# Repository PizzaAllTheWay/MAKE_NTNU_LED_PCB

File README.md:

# MAKE_NTNU_LED_PCB
A light show PCB of LEDs in Real Time, PCB and Firmware made self with the use of external firmware libraries.

https://github.com/PizzaAllTheWay/MAKE_NTNU_LED_PCB/assets/42731091/1496fe23-2bfd-4109-9f32-cd6afeccfe6b

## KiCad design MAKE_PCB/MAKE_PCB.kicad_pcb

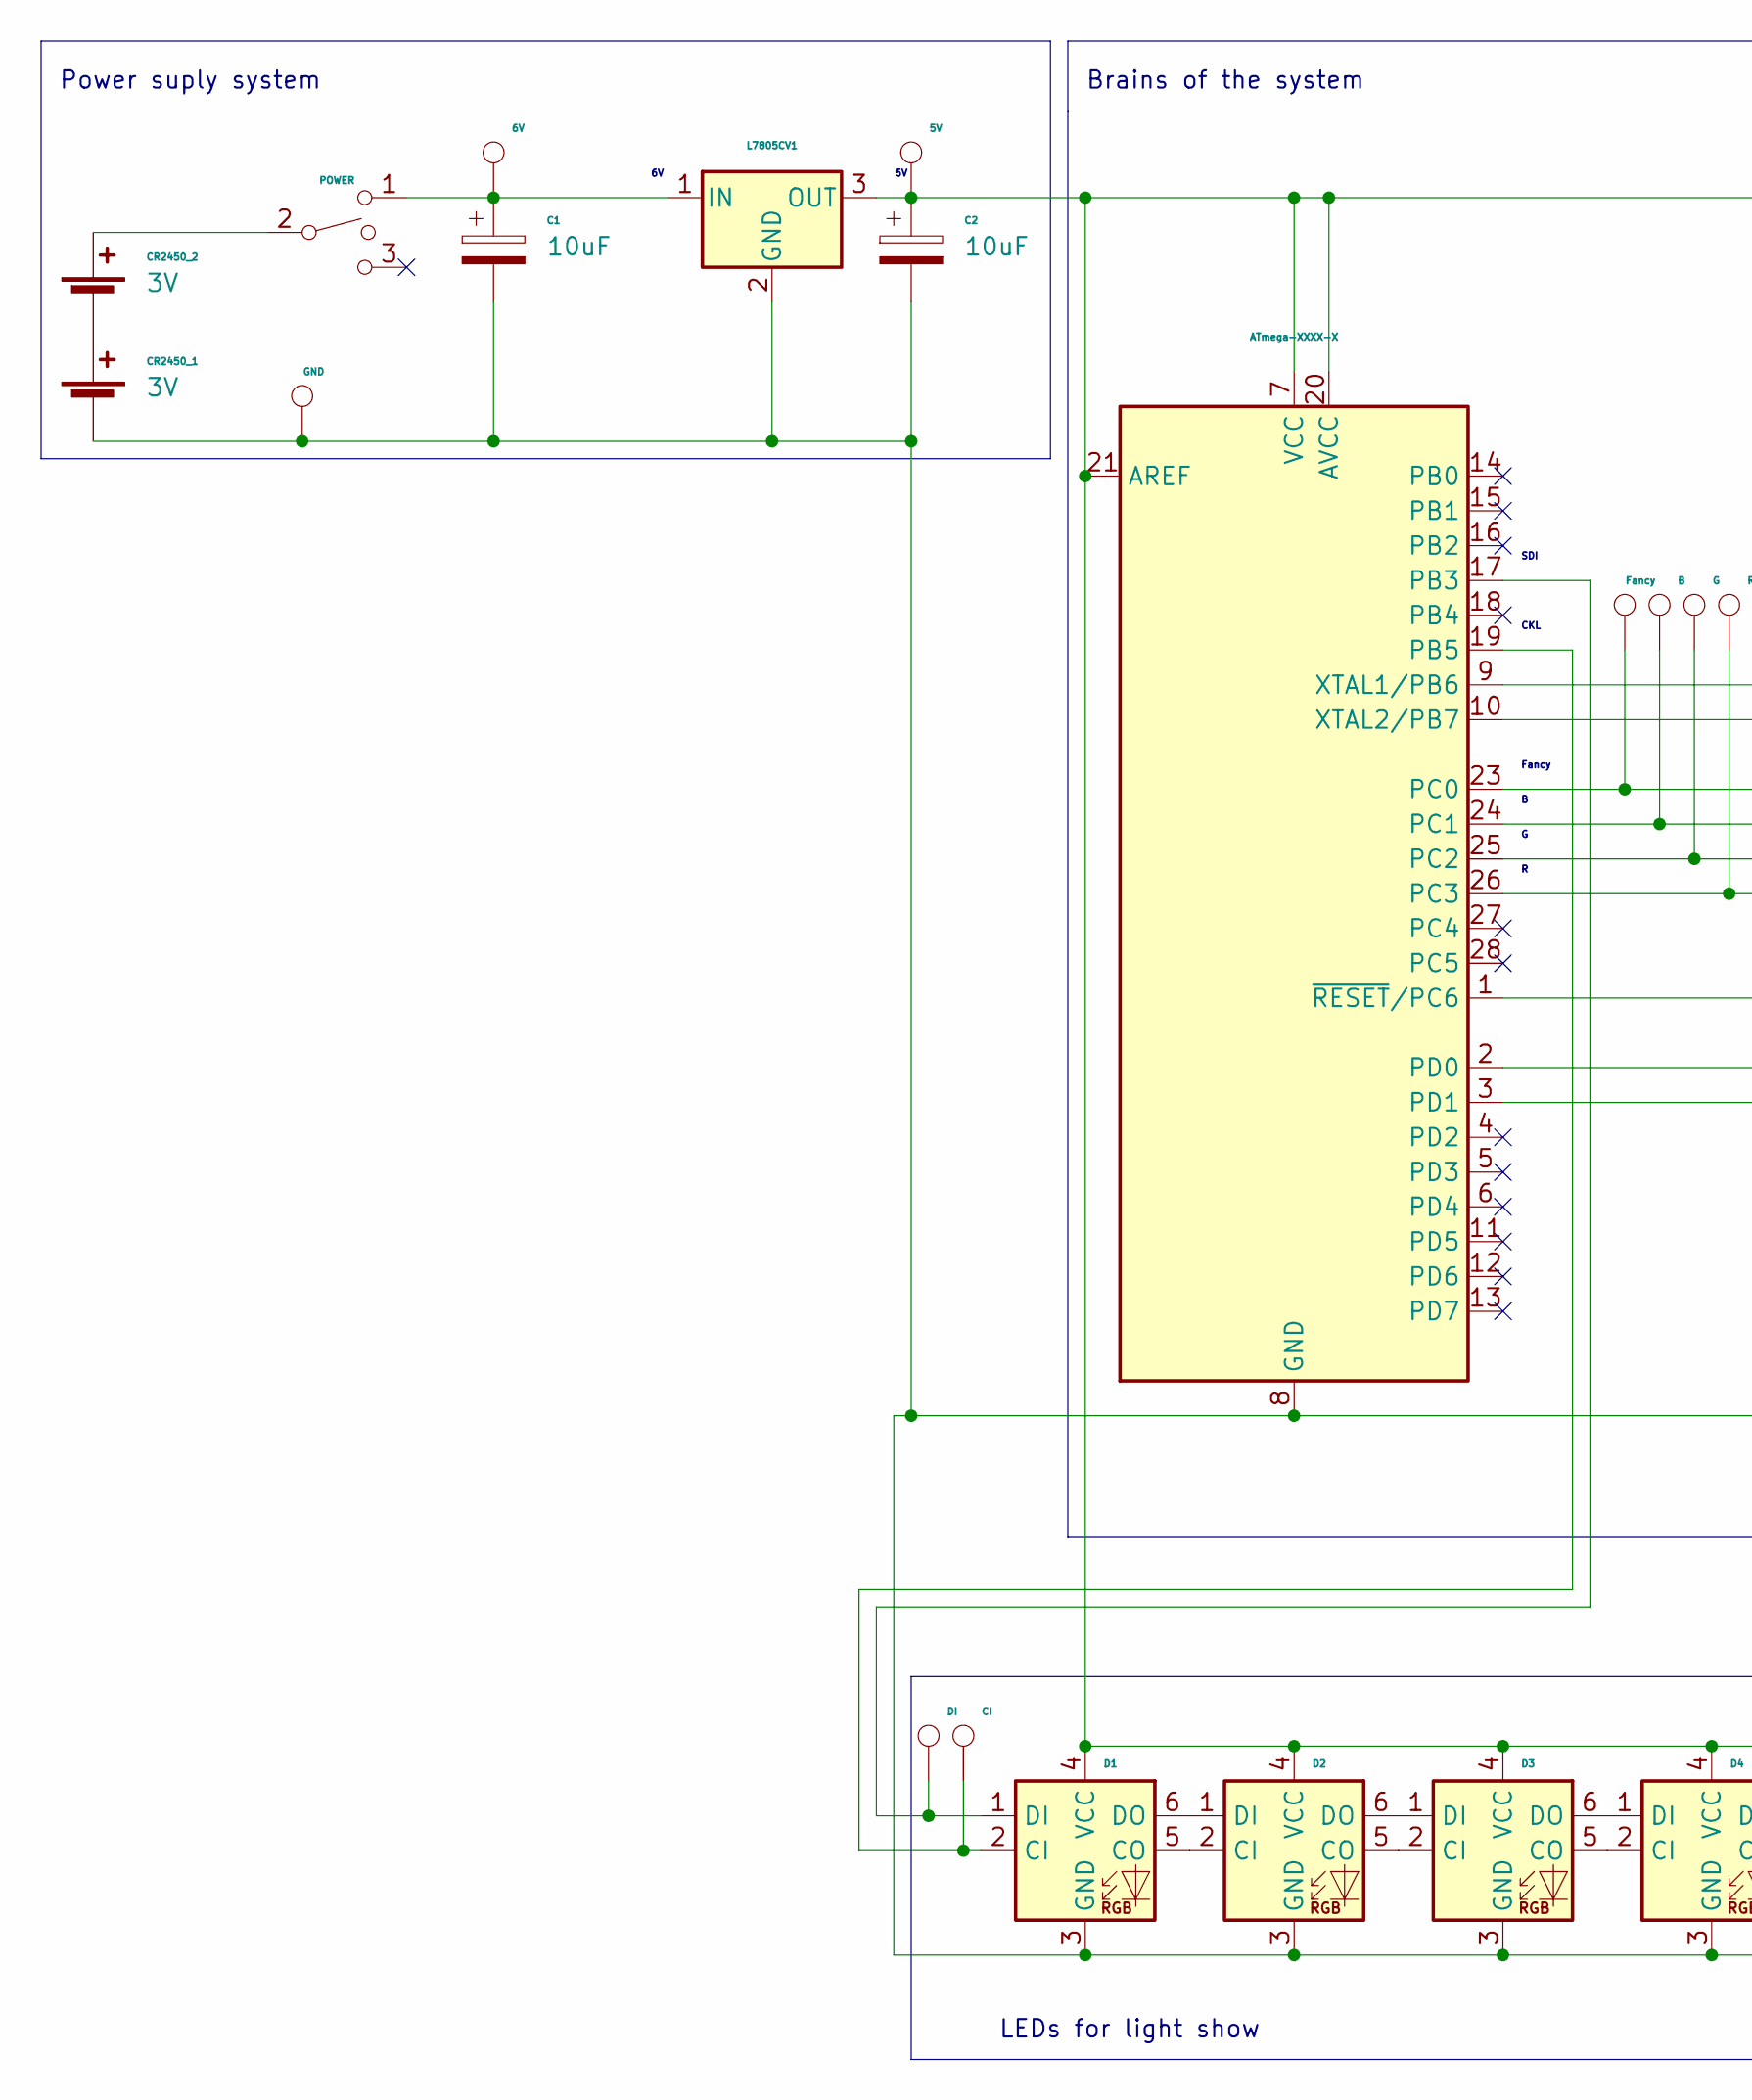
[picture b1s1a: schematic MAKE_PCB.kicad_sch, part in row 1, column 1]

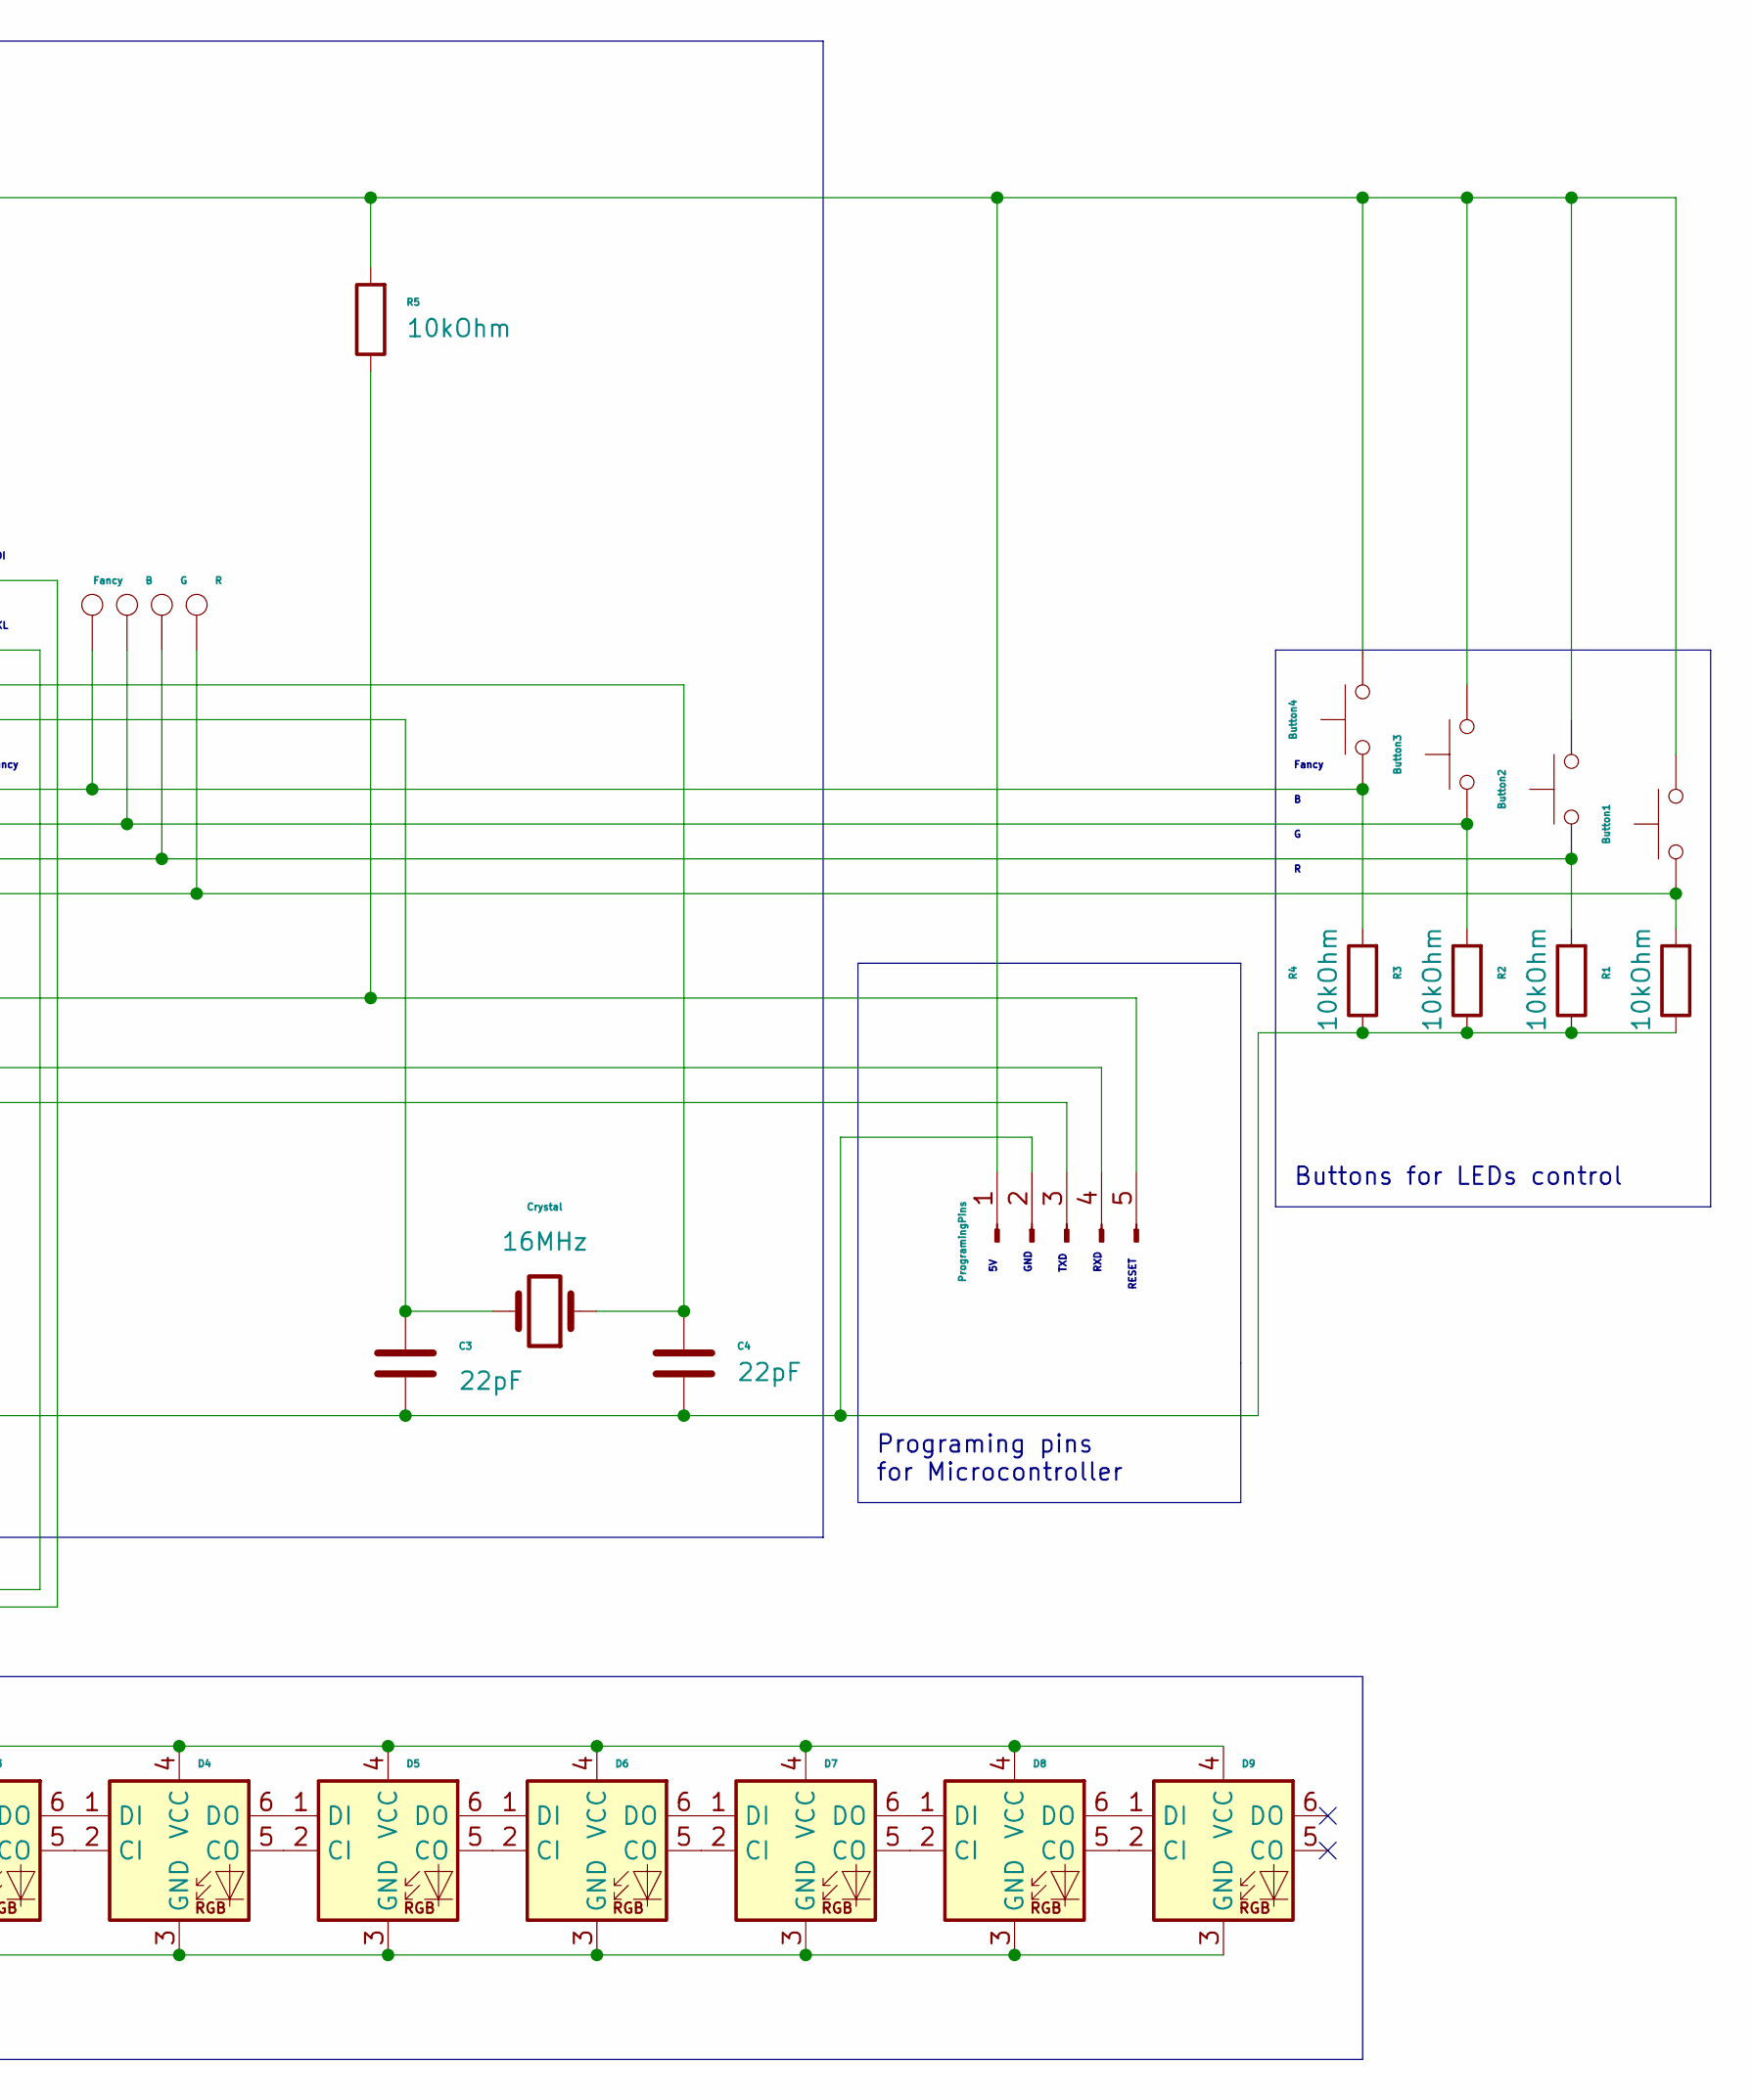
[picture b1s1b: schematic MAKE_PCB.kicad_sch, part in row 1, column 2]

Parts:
5V, 6V: TestPoint; TestPoint_THTPad_D1.0mm_Drill0.5mm
ATmega-XXXX-X: ATmega168V-10P; DIP-28_W7.62mm
B: TestPoint; TestPoint_THTPad_D1.0mm_Drill0.5mm
Button1, Button2, Button3, Button4: SW_Push; Button_2Pins
C1, C2: 10uF; CP_Radial_D5.0mm_P2.50mm
C3, C4: 22pF; C_Disc_D4.3mm_W1.9mm_P5.00mm
CI: TestPoint; TestPoint_THTPad_D1.0mm_Drill0.5mm
CR2450_1, CR2450_2: 3V; BatteryHolder_ComfortableElectronic_CH273-2450_1x2450
Crystal: 16MHz; Crystal_HC49-4H_Vertical
D1, D2, D3, D4, D5, D6, D7, D8, D9: APA102; LED_RGB_5050-6
DI: TestPoint; TestPoint_THTPad_D1.0mm_Drill0.5mm
Fancy: TestPoint; TestPoint_THTPad_D1.0mm_Drill0.5mm
G: TestPoint; TestPoint_THTPad_D1.0mm_Drill0.5mm
GND: TestPoint; TestPoint_THTPad_D1.0mm_Drill0.5mm
L7805CV1: L7805; L7805CV
POWER: SW_SPDT_MSM; SPDT_Switch
ProgramingPins: Conn_01x05_Male; ConnectionPins_5x1
R: TestPoint; TestPoint_THTPad_D1.0mm_Drill0.5mm
R1, R2, R3, R4, R5: 10kOhm; R_Axial_DIN0207_L6.3mm_D2.5mm_P10.16mm_Horizontal

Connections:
unnamed: ATmega-XXXX-X.1 (~RESET/PC6), ProgramingPins.5, R5.1
unnamed: ATmega-XXXX-X.2 (PD0), ProgramingPins.4
unnamed: ATmega-XXXX-X.3 (PD1), ProgramingPins.3
unnamed: ATmega-XXXX-X.9 (XTAL1/PB6), C4.1, Crystal.1
unnamed: ATmega-XXXX-X.10 (XTAL2/PB7), C3.1, Crystal.2
unnamed: ATmega-XXXX-X.17 (PB3), D1.1 (DI), DI.1
unnamed: ATmega-XXXX-X.19 (PB5), CI.1, D1.2 (CI)
unnamed: 5V.1, ATmega-XXXX-X.7 (VCC), ATmega-XXXX-X.20 (AVCC), ATmega-XXXX-X.21 (AREF), Button1.2, Button2.2, Button3.2, Button4.2, C2.1, D1.4 (VCC), D2.4 (VCC), D3.4 (VCC), D4.4 (VCC), D5.4 (VCC), D6.4 (VCC), D7.4 (VCC), D8.4 (VCC), D9.4 (VCC), L7805CV1.3 (OUT), ProgramingPins.1, R5.2
unnamed: ATmega-XXXX-X.8 (GND), ATmega-XXXX-X.22 (GND), C1.2, C2.2, C3.2, C4.2, CR2450_1.2 (-), D1.3 (GND), D2.3 (GND), D3.3 (GND), D4.3 (GND), D5.3 (GND), D6.3 (GND), D7.3 (GND), D8.3 (GND), D9.3 (GND), GND.1, L7805CV1.2 (GND), ProgramingPins.2, R1.1, R2.1, R3.1, R4.1
unnamed: ATmega-XXXX-X.23 (PC0), Button4.1, Fancy.1, R4.2
unnamed: ATmega-XXXX-X.24 (PC1), B.1, Button3.1, R3.2
unnamed: 6V.1, C1.1, L7805CV1.1 (IN), POWER.1
unnamed: CR2450_1.1 (+), CR2450_2.2 (-)
unnamed: CR2450_2.1 (+), POWER.2
unnamed: D1.5 (CO), D2.2 (CI)
unnamed: D1.6 (DO), D2.1 (DI)
unnamed: D2.5 (CO), D3.2 (CI)
unnamed: D2.6 (DO), D3.1 (DI)
unnamed: D3.5 (CO), D4.2 (CI)
unnamed: D3.6 (DO), D4.1 (DI)
unnamed: D4.5 (CO), D5.2 (CI)
unnamed: D4.6 (DO), D5.1 (DI)
unnamed: D5.5 (CO), D6.2 (CI)
unnamed: D5.6 (DO), D6.1 (DI)
unnamed: D6.5 (CO), D7.2 (CI)
unnamed: D6.6 (DO), D7.1 (DI)
unnamed: D7.5 (CO), D8.2 (CI)
unnamed: D7.6 (DO), D8.1 (DI)
unnamed: D8.5 (CO), D9.2 (CI)
unnamed: D8.6 (DO), D9.1 (DI)
unnamed: ATmega-XXXX-X.25 (PC2), Button2.1, G.1, R2.2
unnamed: ATmega-XXXX-X.26 (PC3), Button1.1, R.1, R1.2

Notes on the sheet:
SDI
RXD
Fancy
LEDs for light show
RESET
GND
TXD
Brains of the system
CKL
Buttons for LEDs control
Programing pins for Microcontroller
Power suply system

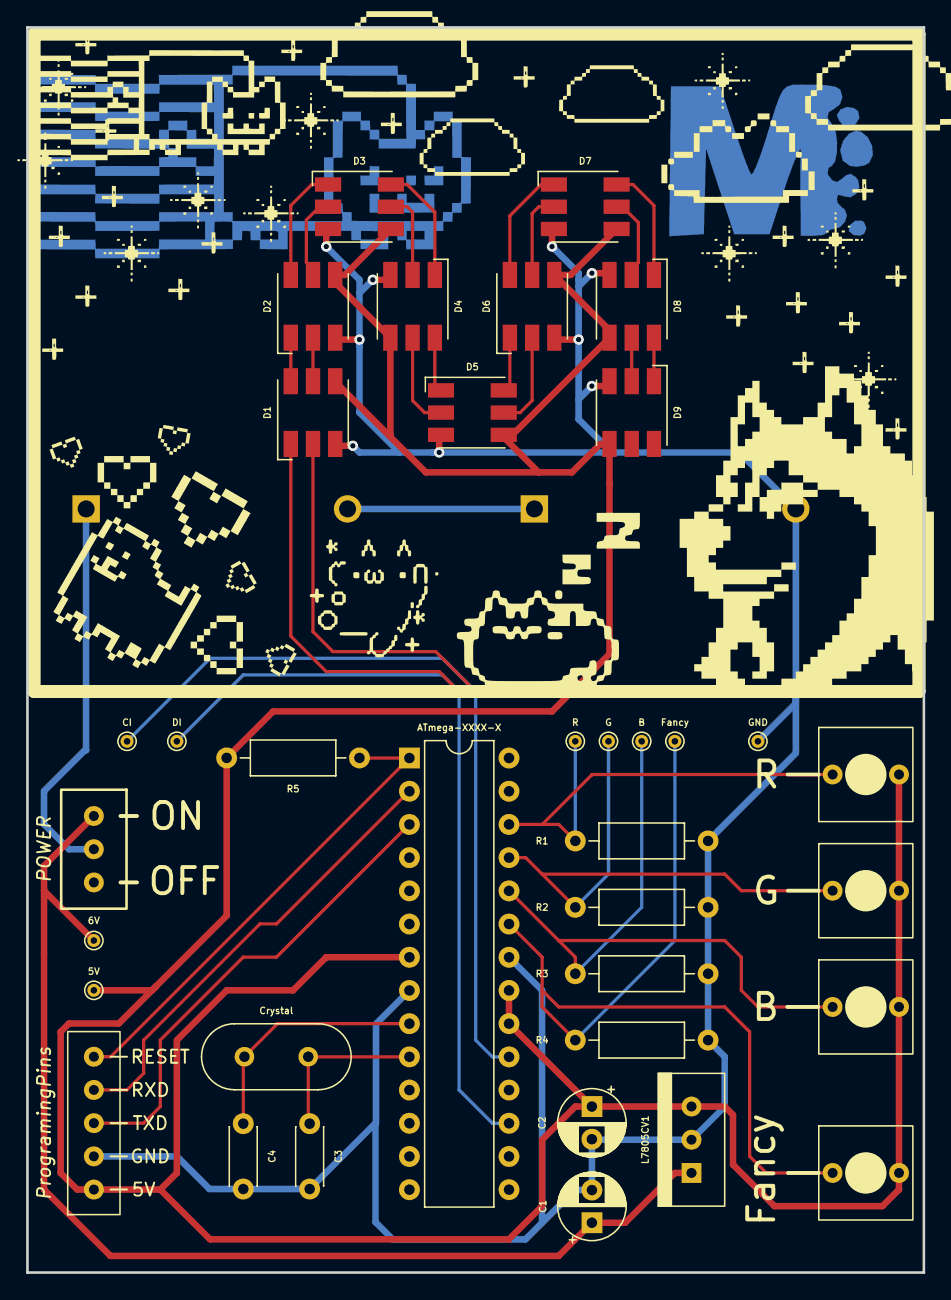
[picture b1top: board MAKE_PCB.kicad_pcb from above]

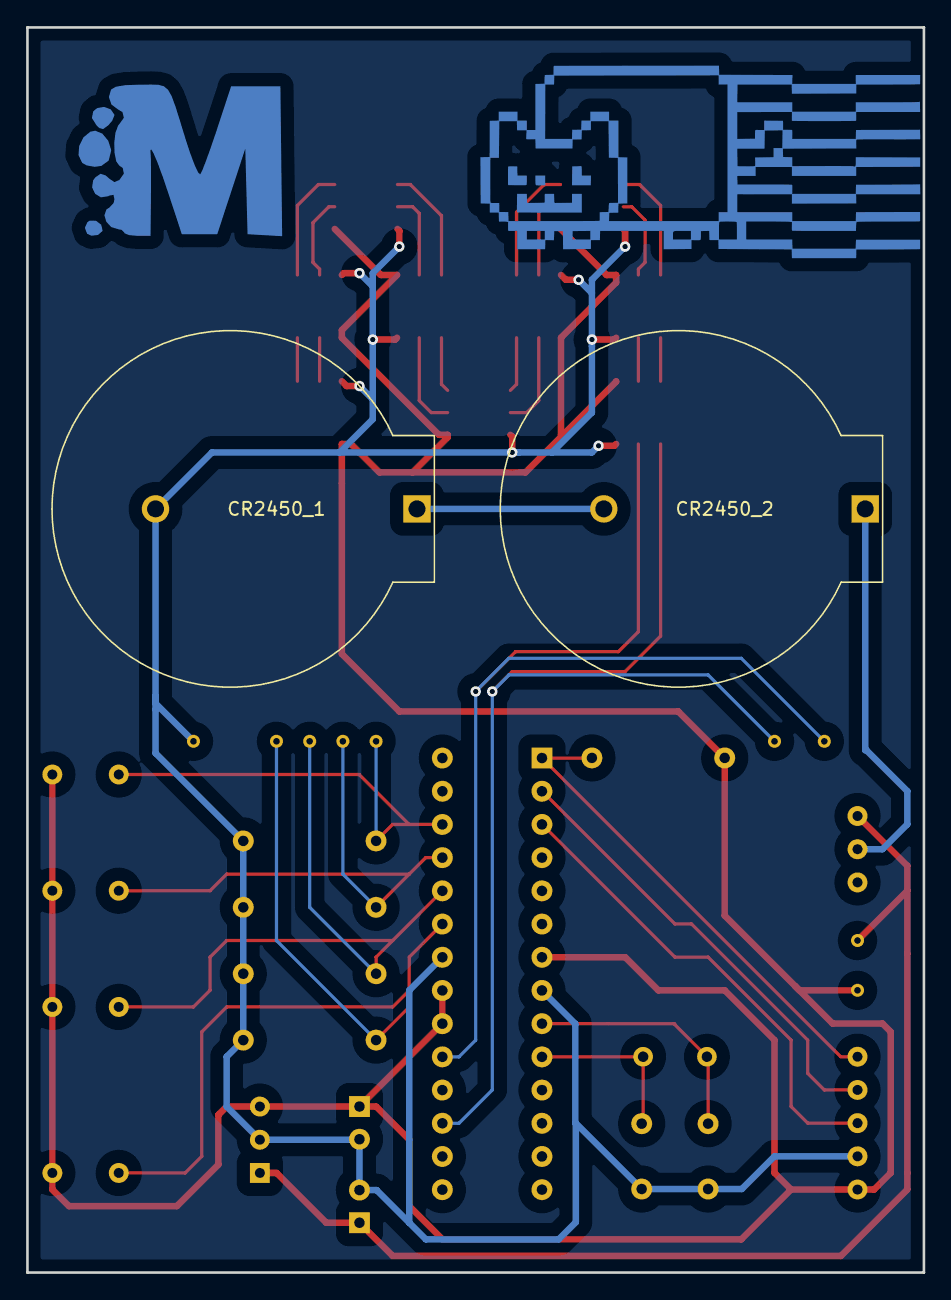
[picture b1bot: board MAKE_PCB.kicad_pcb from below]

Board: 2 copper layers, 68.6 x 95.2 mm, 38 parts (2 on the bottom side), 32 nets.

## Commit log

2023-04-12 Add files via upload
    Added all the files :)
2023-04-12 Create README.md
    Read me :)
2023-12-02 Update README.md
    Added the video showcase that i forgot to include 2 years ago lul X)))))
